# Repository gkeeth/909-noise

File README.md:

# 909-noise

Noise generator module for TR-909 drums. The form factor is a small
(20mm x 30mm) plug in module. Replicates the original LFSR design using a small
microcontroller.

Inputs: 12V, GND

Outputs: white noise signal equivalent to output from 909 shift register (12V
voltage level).

## License
Hardware design files are licensed under a [Creative Commons Attribution-ShareAlike 4.0
International License][cc-by-sa].

[![CC BY-SA 4.0][cc-by-sa-image]][cc-by-sa]

Code is licensed under the MIT license.
[Greatest](https://github.com/silentbicycle/greatest) is licensed under ISC license.

[![License: MIT][mit-shield]][mit-link]

[cc-by-sa]: http://creativecommons.org/licenses/by-sa/4.0/
[cc-by-sa-image]: https://licensebuttons.net/l/by-sa/4.0/88x31.png
[cc-by-sa-shield]: https://img.shields.io/badge/License-CC%20BY--SA%204.0-lightgrey.svg
[mit-link]: https://opensource.org/licenses/MIT
[mit-shield]: https://img.shields.io/badge/License-MIT-yellow.svg

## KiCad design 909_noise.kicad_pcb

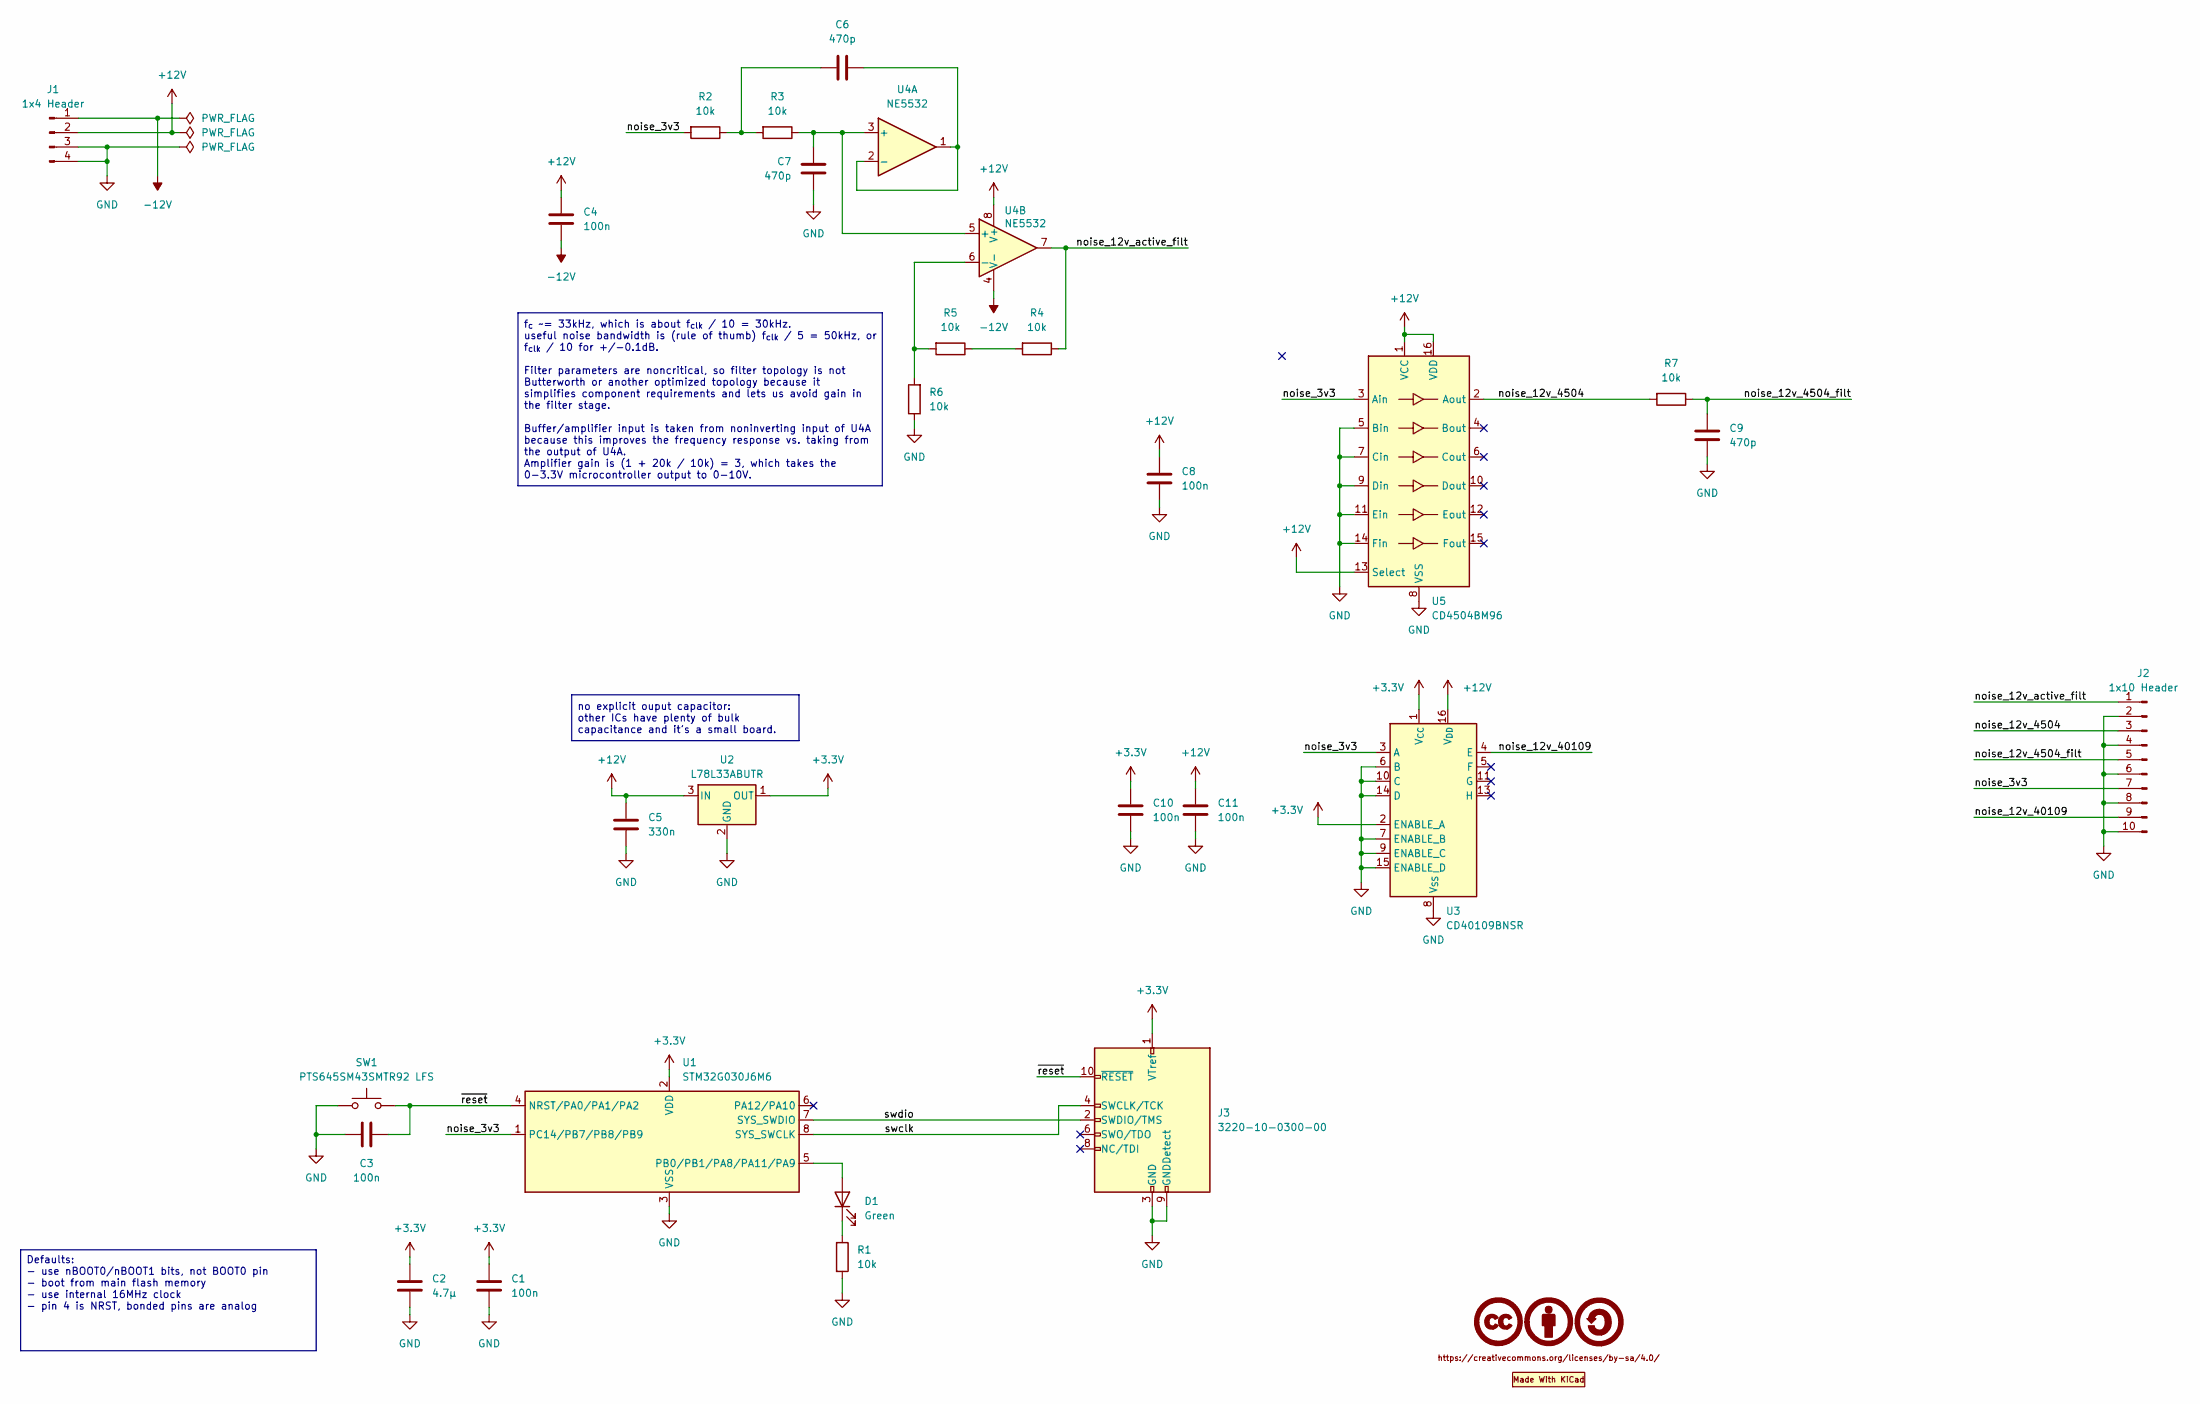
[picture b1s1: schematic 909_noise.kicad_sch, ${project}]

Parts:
C1, C3, C4, C8, C10, C11: 100n; C_0603_1608Metric; Tolerance 10%; Voltage Rating 50V
C2: 4.7μ; C_0805_2012Metric; Tolerance 10%; Voltage Rating 50V
C5: 330n; C_0603_1608Metric; Tolerance 10%; Voltage Rating 50V
C6, C7, C9: 470p; C_0603_1608Metric; Tolerance 5%; Voltage Rating 50V
D1: Green; LED_0603_1608Metric; Forward Voltage 2V; MPN LTST-C191KGKT
J1: 1x4 Header; PinHeader_1x04_P2.54mm_Vertical
J2: 1x10 Header; PinHeader_1x10_P2.54mm_Vertical
J3: 3220-10-0300-00; CNC_Tech_3220-10-0300-00_2x05_P1.27mm_Vertical; MPN 3220-10-0300-00
LOGO1: CC-BY-SA; CC-BY-SA_SilkScreenTop_Small
LOGO2: Made With KiCad; KiCad-Logo2_5mm_SilkScreen
R1, R2, R3, R4, R5, R6, R7: 10k; R_0603_1608Metric; Tolerance 1%; Power Rating 0.1W
SW1: PTS645SM43SMTR92 LFS; SW_SPST_PTS645; MPN PTS645SM43SMTR92 LFS
U1: STM32G030J6M6; SOIC-8_3.9x4.9mm_P1.27mm; MPN STM32G030J6M6
U2: L78L33ABUTR; SOT-89-3; Output Voltage 3.3V; MPN L78L33ABUTR
U3: CD40109BNSR; SOIC-16W_5.3x10.2mm_P1.27mm; MPN CD40109BNSR
U4: NE5532; SOIC-8_3.9x4.9mm_P1.27mm
U5: CD4504BM96; SOIC-16_3.9x9.9mm_P1.27mm; MPN CD4504BM96

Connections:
+3.3V: C1.2, C2.2, C10.2, J3.1 (VTref), U1.2 (VDD), U2.1 (OUT), U3.1 (V_{CC}), U3.2 (ENABLE_A)
+12V: C4.2, C5.2, C8.2, C11.2, J1.2, U2.3 (IN), U3.16 (V_{DD}), U4.8 (V+), U5.1 (VCC), U5.13 (Select), U5.16 (VDD)
-12V: C4.1, J1.1, U4.4 (V-)
/noise_3v3: J2.7, R2.2, U1.1 (PC14/PB7/PB8/PB9), U3.3 (A), U5.3 (Ain)
/noise_12v_4504: J2.3, R7.2, U5.2 (Aout)
/noise_12v_4504_filt: C9.1, J2.5, R7.1
/noise_12v_40109: J2.9, U3.4 (E)
/noise_12v_active_filt: J2.1, R4.1, U4.7
/swclk: J3.4 (SWCLK/TCK), U1.8 (SYS_SWCLK)
/swdio: J3.2 (SWDIO/TMS), U1.7 (SYS_SWDIO)
/~reset: C3.2, J3.10 (~RESET), SW1.2, U1.4 (NRST/PA0/PA1/PA2)
GND: C1.1, C2.1, C3.1, C5.1, C7.2, C8.1, C9.2, C10.1, C11.1, J1.3, J1.4, J2.2, J2.4, J2.6, J2.8, J2.10, J3.3 (GND), J3.5 (GND), J3.9 (GNDDetect), R1.2, R6.1, SW1.1, U1.3 (VSS), U2.2 (GND), U3.6 (B), U3.7 (ENABLE_B), U3.8 (V_{SS}), U3.9 (ENABLE_C), U3.10 (C), U3.14 (D), U3.15 (ENABLE_D), U5.5 (Bin), U5.7 (Cin), U5.8 (VSS), U5.9 (Din), U5.11 (Ein), U5.14 (Fin)
unnamed: C6.1, R2.1, R3.2
unnamed: D1.2 (A), U1.5 (PB0/PB1/PA8/PA11/PA9)
unnamed: D1.1 (K), R1.1
unnamed: R4.2, R5.1
unnamed: C7.1, R3.1, U4.3 (+), U4.5 (+)
unnamed: C6.2, U4.1, U4.2 (-)
unnamed: R5.2, R6.2, U4.6 (-)

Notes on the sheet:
f_{c} ~= 33kHz, which is about f_{clk} / 10 = 30kHz. useful noise bandwidth is (rule of thumb) f_{clk} / 5 = 50kHz, or f_{clk} / 10 for +/-0.1dB. Filter parameters are noncritical, so filter topology is not Butterworth or another optimized topology because it simplifies component requirements and l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
no explicit ouput capacitor: other ICs have plenty of bulk capacitance and it's a small board.
Defaults: - use nBOOT0/nBOOT1 bits, not BOOT0 pin - boot from main flash memory - use internal 16MHz clock - pin 4 is NRST, bonded pins are analog

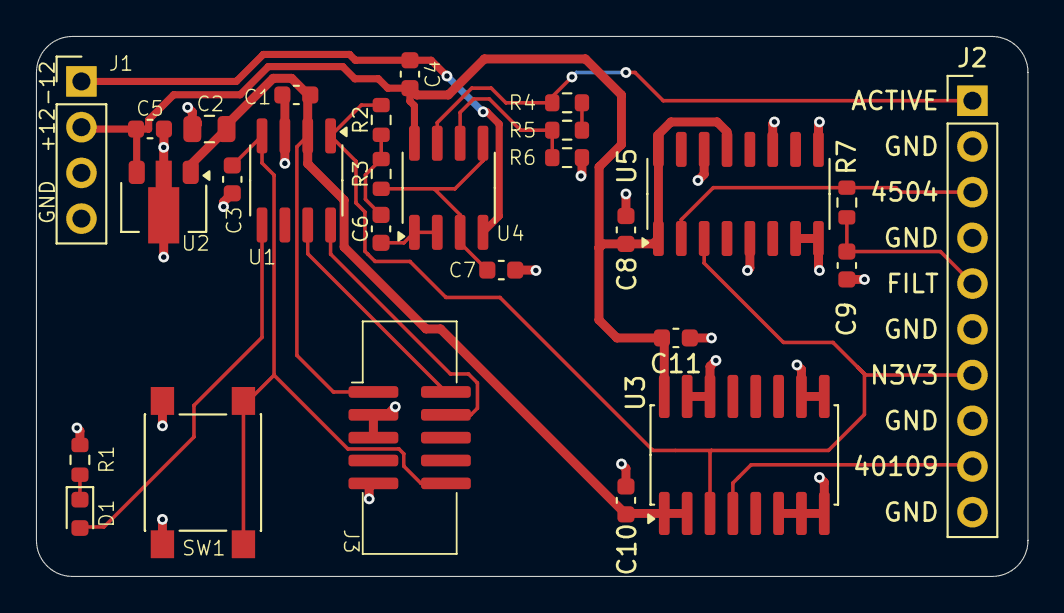
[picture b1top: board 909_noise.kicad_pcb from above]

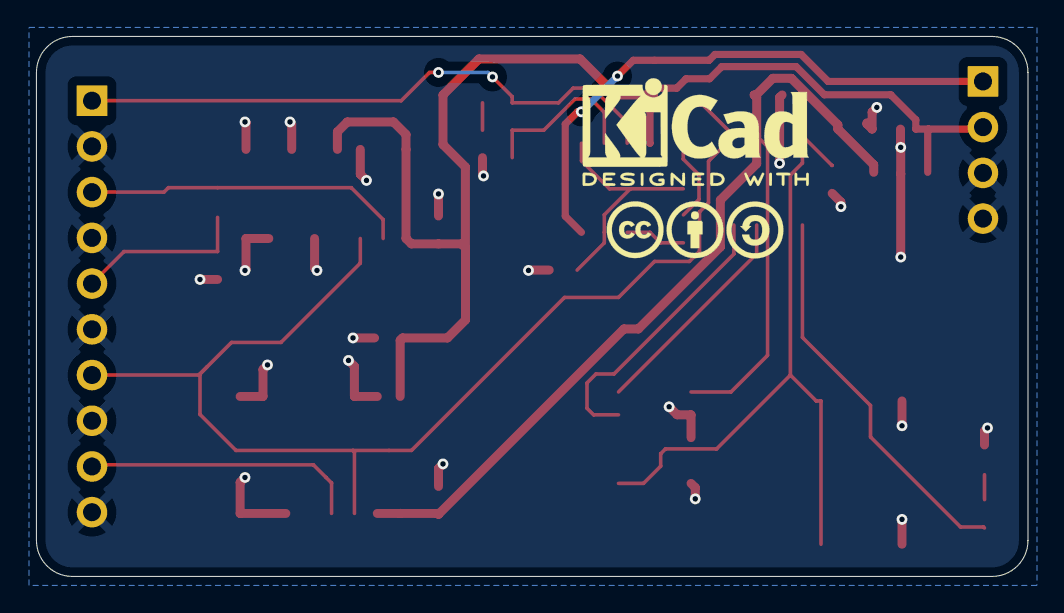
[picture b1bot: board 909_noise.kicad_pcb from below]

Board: 2 copper layers, 55.1 x 30.0 mm, 30 parts (2 on the bottom side), 19 nets.

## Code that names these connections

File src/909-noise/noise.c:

// example based on libopencm3 miniblink/systick_blink/button examples

#include <libopencm3/stm32/rcc.h>
#include <libopencm3/stm32/gpio.h>
#include <libopencm3/stm32/timer.h>
#include <libopencm3/cm3/nvic.h>
#include <libopencm3/cm3/systick.h>

#include "lfsr.h"

// LED is PB0/PB1/PA8/PA11/PA9, and we pick PB0
#define PORT_LED GPIOB
#define PIN_LED GPIO0 // noise pin is PC14/PB7/PB8/PB9, and we pick PB7
#define PORT_NOISE GPIOB
#define PIN_NOISE GPIO7
#define TIM_NOISE TIM3

volatile uint32_t counter = 0;

void tim34_isr(void) {
    if (timer_interrupt_source(TIM_NOISE, TIM_SR_UIF)) {
        static uint32_t lfsr = 0xFFFFFFFF;
        uint32_t output;
        lfsr_step(&lfsr, &output);
        if (output) {
            gpio_set(PORT_NOISE, PIN_NOISE);
        } else {
            gpio_clear(PORT_NOISE, PIN_NOISE);
        }

        timer_clear_flag(TIM_NOISE, TIM_SR_UIF);
    }
}

void sys_tick_handler(void) {
    ++counter;
}

uint32_t millis(void);
uint32_t millis(void) {
    return counter;
}

static void setup(void) {
    rcc_clock_setup(&rcc_clock_config[RCC_CLOCK_CONFIG_HSI_PLL_64MHZ]);

    STK_CVR = 0; // clear systick current value to start immediately

    // every 1 ms (1000 Hz)
    systick_set_frequency(1000, rcc_ahb_frequency);
    systick_counter_enable();
    systick_interrupt_enable();

    // setup LED pins
    rcc_periph_clock_enable(RCC_GPIOB);
    // set LED pins to output push-pull
    gpio_mode_setup(PORT_LED, GPIO_MODE_OUTPUT, GPIO_PUPD_NONE, PIN_LED);

    // setup noise pin
    gpio_mode_setup(PORT_NOISE, GPIO_MODE_OUTPUT, GPIO_PUPD_NONE, PIN_NOISE);

    // setup timer
    rcc_periph_clock_enable(RCC_TIM3);
    // rcc_ahb_frequency = 64MHz
    // desired noise fclk = ~300kHz
    // period of 213 - 1 gives 300.5kHz
    timer_set_prescaler(TIM_NOISE, 0);
    timer_set_period(TIM_NOISE, 212);
    timer_enable_irq(TIM_NOISE, TIM_DIER_UIE);
    nvic_enable_irq(NVIC_TIM34_IRQ);
    timer_enable_counter(TIM_NOISE);
}


int main(void) {
    setup();

    const uint32_t BLINK_DELAY = 500;
    uint32_t last_flash_millis = millis();

    while(1) {
        if ((millis() - last_flash_millis) > BLINK_DELAY) {
            gpio_toggle(PORT_LED, PIN_LED);
            last_flash_millis = millis();
        }
    }

    return 0;
}

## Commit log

2024-05-05 inital commit with schematic
2024-05-05 initial placement, schematic tweaks
2024-05-05 add output filter
2024-05-05 quick silk adjust
2024-05-05 add netclasses and a gnd fill
2024-05-05 initial layout
2024-05-05 fillet board outline
2024-05-05 flip connectors to bottom
2024-05-05 adjust connector position and add connector dims
2024-05-05 add decals to back of board, rearrange silk slightly
2024-05-05 change to cheaper debug connector
2024-05-05 add readme
2024-05-05 fix line break in readme
2024-05-05 fix pads somehow not having mask/paste layers
2024-05-05 add github url and update back silkscreen
2024-05-05 cleanup footprint attributes between pcb and sch
2024-05-09 tweak silk and footprint placement
2024-05-10 fix overlapping courtyards
2024-05-10 add Makefile
2024-05-19 swap symbols for specified symbols from dblib
2024-09-22 update license info
2024-09-22 add libopencm3 and a working blink example
2024-09-24 initial noise application (just square wave)
2024-09-25 add LFSR implementation
2024-09-25 add sim of clock oscillator from original 909
2024-09-25 ignore generated files
2024-09-25 add initial unit testing
2024-11-27 routed with single-supply +12V on opamp
2024-11-27 add -12V to opamp
2024-11-27 remove screenshot from schematic
2024-11-27 update issue date in schematic and board
2024-12-05 fix netclass assignments
2024-12-05 adjust routing for minimizing ground plane interruption
2025-03-16 fix include paths for language server
2025-03-16 fixup unit test framework
2025-03-16 Move LFSR to a separate module and test it
2025-03-23 Specify an openocd cfg in makefile so we can flash
2025-03-29 save in kicad 9
2025-03-29 clarify comment about clock frequency
2025-03-29 Reorganize main (no functional change)
2025-07-16 add jobset for outputs
2025-07-16 r0.3 schematic/layout
    - change active filter values to filter at lower freq
    - add raw 3V3 output
    - add two types of level shifters to 12V
    - add passively filtered 12V output
2025-07-16 add jlc order number locator
2025-07-16 add noise spectrum analysis/plotting script

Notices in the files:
909_noise.kicad_sch:
https://creativecommons.org/licenses/by-sa/4.0
parts and their libraries:
https://creativecommons.org/licenses/by-sa/4.0/deed.en
\"CC-BY-SA\" license graphic, silkscreen, 3mm tall
